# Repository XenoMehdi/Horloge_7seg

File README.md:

# Horloge_7seg
Affichage Horloge, calendrier et température sur un afficheur 7 segments LED geant

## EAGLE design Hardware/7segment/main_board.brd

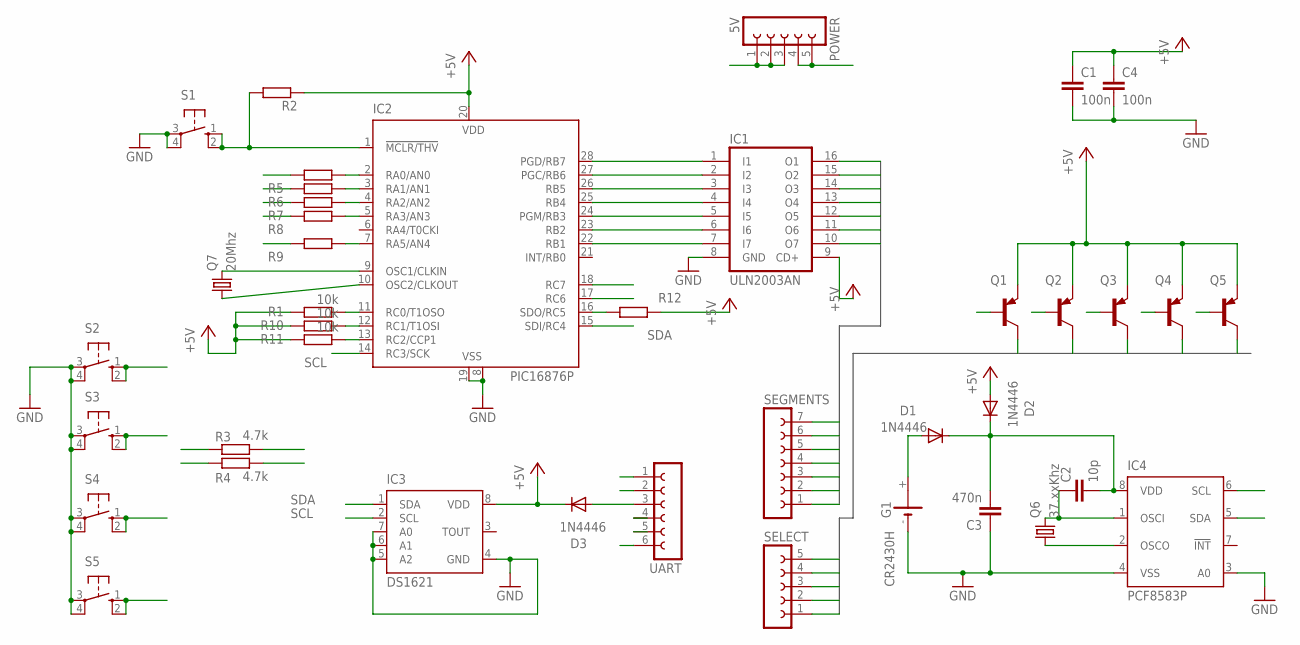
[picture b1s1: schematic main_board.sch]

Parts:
C1, C4: 100n; C025-030X050
C2: 10p; C025-030X050
C3: 470n; C025-030X050
D1, D2, D3: 1N4446; DO35-10
G1: CR2430H
IC1: ULN2003AN; DIL16
IC2: PIC16876P; DIL28-3
IC3: DS1621; DIL08
IC4: PCF8583P; DIL08
POWER: 5V; FE05-1
Q1, Q2, Q3, Q4, Q5: BC369; TO92-BCE
Q6: 37.xxKhz; TC38H
Q7: 20Mhz; HC49U-V
R1, R10, R11: 10k; 0204/7
R2, R5, R6, R7, R8, R9, R12: R-EU_0204/7; 0204/7
R3, R4: 4.7k; 0204/7
S1, S2, S3, S4, S5: 10-XX; B3F-10XX
SEGMENTS: FE07-1; FE07
SELECT: FE05-1
UART: FE06-1; FE06

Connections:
+5V: C1.1, C4.1, D2.A, D3.C, IC1.9 (CD+), IC2.20 (VDD), IC3.8 (VDD), POWER.1, POWER.2, POWER.3, Q1.E, Q2.E, Q3.E, Q4.E, Q5.E, R1.2, R2.1, R3.1, R4.1, R10.2, R11.2, R12.1
GND: C1.2, C3.1, C4.2, G1.-, IC1.8 (GND), IC2.8 (VSS), IC2.19 (VSS), IC3.4 (GND), IC3.5 (A2), IC3.6 (A1), IC3.7 (A0), IC4.3 (A0), IC4.4 (VSS), POWER.4, POWER.5, S1.3, S1.4 (P1), S2.3, S2.4 (P1), S3.3, S3.4 (P1), S4.3, S4.4 (P1), S5.3, S5.4 (P1), UART.1
J_SEG_DATA0: IC1.16 (O1), SEGMENTS.7
J_SEG_DATA1: IC1.15 (O2), SEGMENTS.6
J_SEG_DATA2: IC1.14 (O3), SEGMENTS.5
J_SEG_DATA3: IC1.13 (O4), SEGMENTS.4
J_SEG_DATA4: IC1.12 (O5), SEGMENTS.3
J_SEG_DATA5: IC1.11 (O6), SEGMENTS.2
J_SEG_DATA6: IC1.10 (O7), SEGMENTS.1
J_SEG_SELECT0: Q1.C, SELECT.5
J_SEG_SELECT1: Q2.C, SELECT.4
J_SEG_SELECT2: Q3.C, SELECT.3
J_SEG_SELECT3: Q4.C, SELECT.2
J_SEG_SELECT4: Q5.C, SELECT.1
unnamed: IC1.1 (I1), IC2.28 (PGD/RB7)
unnamed: IC1.2 (I2), IC2.27 (PGC/RB6)
unnamed: IC1.3 (I3), IC2.26 (RB5)
unnamed: IC1.4 (I4), IC2.25 (RB4)
unnamed: IC1.5 (I5), IC2.24 (PGM/RB3)
unnamed: C2.1, IC4.1 (OSCI), Q6.2
unnamed: IC1.7 (I7), IC2.22 (RB1)
unnamed: IC2.1 (!MCLR/THV), R2.2, S1.1 (S), S1.2 (S1)
unnamed: IC2.2 (RA0/AN0), R5.1
unnamed: IC2.10 (OSC2/CLKOUT), Q7.1
unnamed: IC4.2 (OSCO), Q6.1
unnamed: D1.A, G1.+
unnamed: IC1.6 (I6), IC2.23 (RB2)
unnamed: C2.2, C3.2, D1.C, D2.C, IC4.8 (VDD)
unnamed: IC2.9 (OSC1/CLKIN), Q7.2
unnamed: IC2.3 (RA1/AN1), R6.1
unnamed: IC2.4 (RA2/AN2), R7.1
unnamed: IC2.5 (RA3/AN3), R8.1
unnamed: IC2.7 (RA5/AN4), R9.1
unnamed: D3.A, UART.3
SCL: IC2.14 (RC3/SCK), IC3.2 (SCL), IC4.6 (SCL), R4.2
SDA: IC2.15 (SDI/RC4), IC3.1 (SDA), IC4.5 (SDA), R3.2
SEG1: Q1.B, R5.2
SEG2: Q2.B, R6.2
SEG3: Q3.B, R7.2
SEG4: Q4.B, R8.2
SEG5: Q5.B, R9.2
SW1: IC2.11 (RC0/T1OSO), R1.1, S2.1 (S), S2.2 (S1)
SW2: IC2.12 (RC1/T1OSI), R10.1, S3.1 (S), S3.2 (S1)
SW3: IC2.13 (RC2/CCP1), R11.1, S4.1 (S), S4.2 (S1)
SW4: IC2.16 (SDO/RC5), R12.2, S5.1 (S), S5.2 (S1)
UART_RX: IC2.18 (RC7), UART.4
UART_TX: IC2.17 (RC6), UART.5

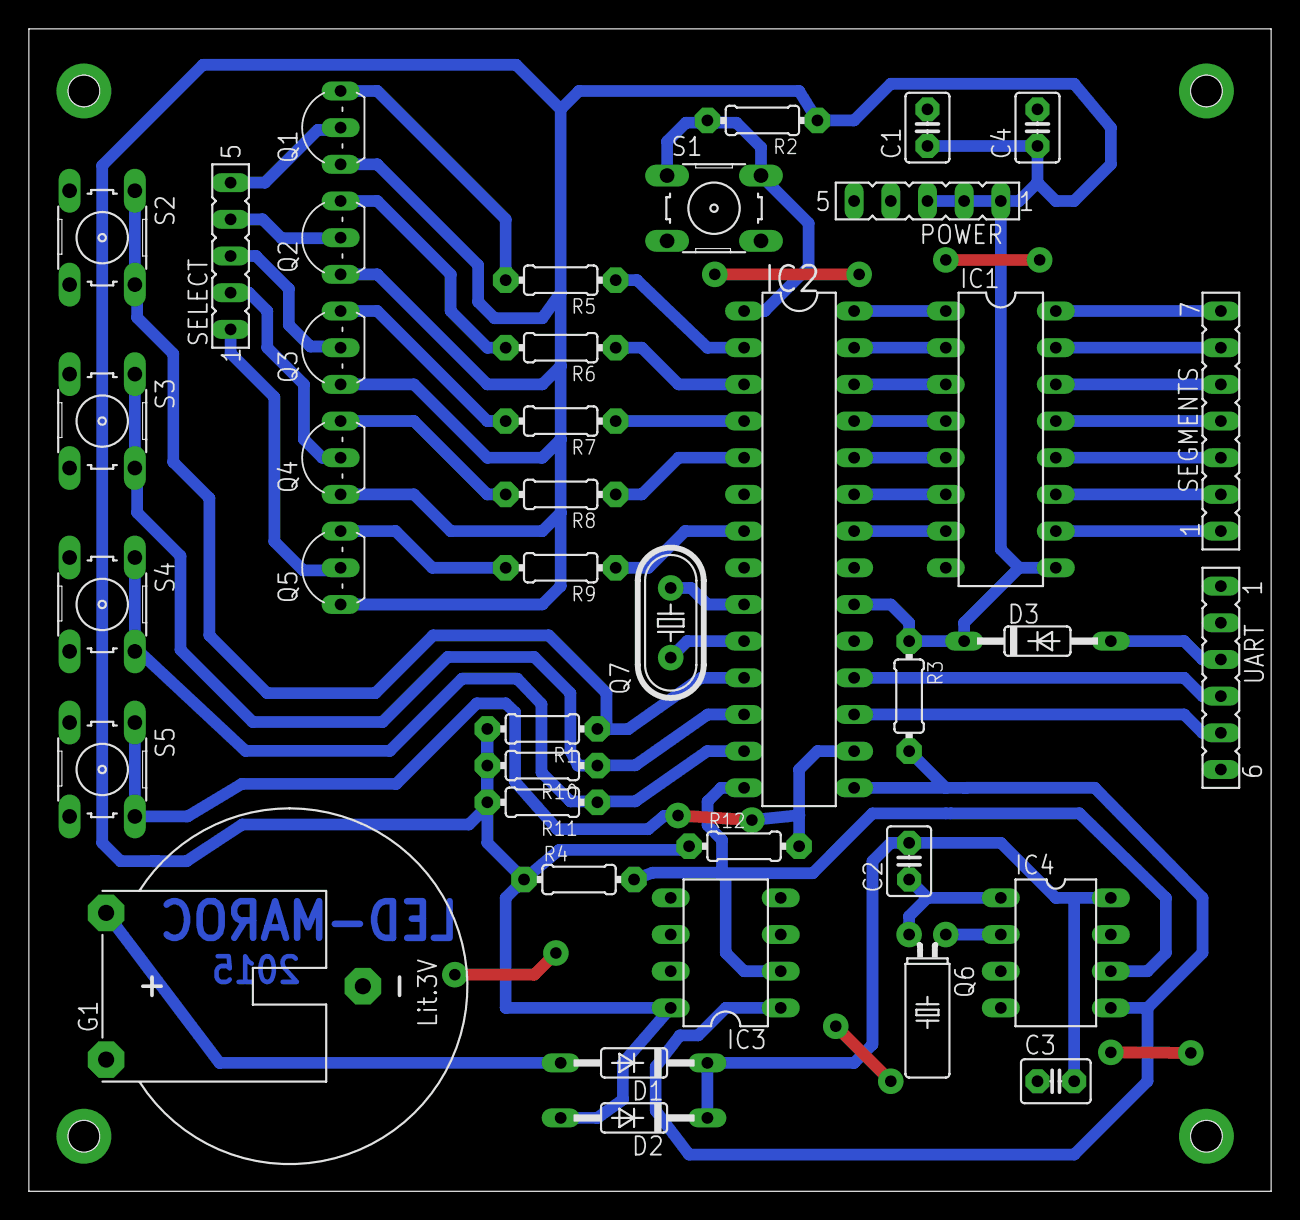
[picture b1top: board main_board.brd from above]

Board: 2 copper layers, 86.0 x 80.5 mm, 40 parts (0 on the bottom side), 47 nets.

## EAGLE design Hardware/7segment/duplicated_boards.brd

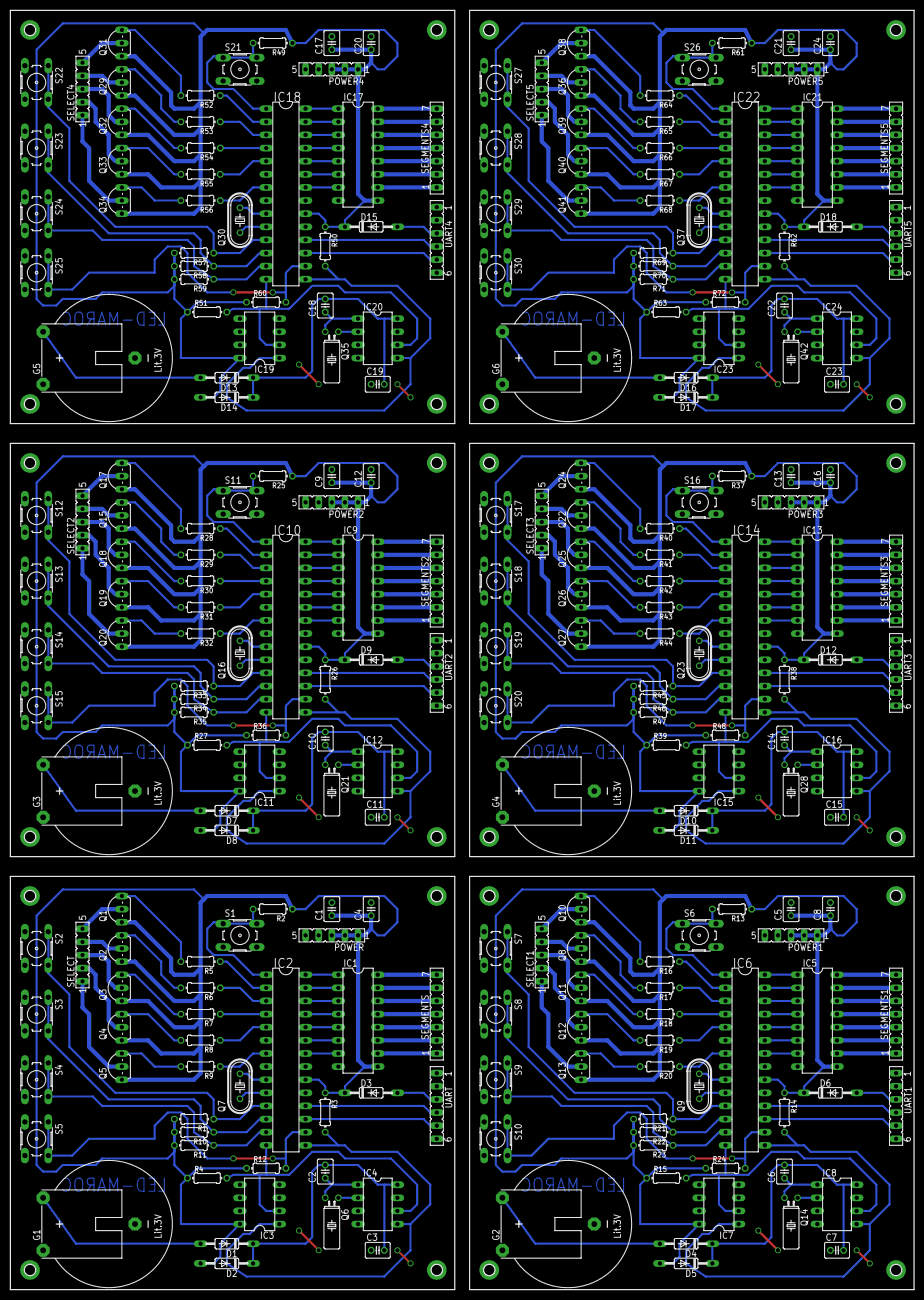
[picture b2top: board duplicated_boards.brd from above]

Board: 2 copper layers, 174.9 x 247.6 mm, 240 parts (0 on the bottom side), 282 nets.

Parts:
C1, C4, C5, C8, C9, C12, C13, C16, C17, C20, C21, C24: 100n; C025-030X050
C2, C6, C10, C14, C18, C22: 10p; C025-030X050
C3, C7, C11, C15, C19, C23: 470n; C025-030X050
D1, D2, D3, D4, D5, D6, D7, D8, D9, D10, D11, D12, D13, D14, D15, D16, D17, D18: 1N4446; DO35-10
G1, G2, G3, G4, G5, G6: CR2430H
IC1, IC5, IC9, IC13, IC17, IC21: ULN2003AN; DIL16
IC2, IC6, IC10, IC14, IC18, IC22: PIC16876P; DIL28-3
IC3, IC7, IC11, IC15, IC19, IC23: DS1621; DIL08
IC4, IC8, IC12, IC16, IC20, IC24: PCF8583P; DIL08
POWER, POWER1, POWER2, POWER3, POWER4, POWER5: 5V; FE05-1
Q1, Q2, Q3, Q4, Q5, Q8, Q10, Q11, Q12, Q13, Q15, Q17, Q18, Q19, Q20, Q22, Q24, Q25, Q26, Q27, Q29, Q31, Q32, Q33, Q34, Q36, Q38, Q39, Q40, Q41: BC369; TO92-BCE
Q6, Q14, Q21, Q28, Q35, Q42: 37.xxKhz; TC38H
Q7, Q9, Q16, Q23, Q30, Q37: 20Mhz; HC49U-V
R1, R10, R11, R21, R22, R23, R33, R34, R35, R45, R46, R47, R57, R58, R59, R69, R70, R71: 10k; 0204/7
R2, R5, R6, R7, R8, R9, R12, R13, R16, R17, R18, R19, R20, R24, R25, R28, R29, R30, R31, R32, R36, R37, R40, R41, R42, R43, R44, R48, R49, R52, R53, R54, R55, R56, R60, R61, R64, R65, R66, R67, R68, R72: 0204/7
R3, R4, R14, R15, R26, R27, R38, R39, R50, R51, R62, R63: 4.7k; 0204/7
S1, S2, S3, S4, S5, S6, S7, S8, S9, S10, S11, S12, S13, S14, S15, S16, S17, S18, S19, S20, S21, S22, S23, S24, S25, S26, S27, S28, S29, S30: B3F-10XX
SEGMENTS, SEGMENTS1, SEGMENTS2, SEGMENTS3, SEGMENTS4, SEGMENTS5: FE07
SELECT, SELECT1, SELECT2, SELECT3, SELECT4, SELECT5: FE05-1
UART, UART1, UART2, UART3, UART4, UART5: FE06

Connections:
+5V: C1.1, C4.1, D2.A, D3.C, IC1.9, IC2.20, IC3.8, POWER.1, POWER.2, POWER.3, Q1.E, Q2.E, Q3.E, Q4.E, Q5.E, R1.2, R2.1, R3.1, R4.1, R10.2, R11.2, R12.1
+5V1: C5.1, C8.1, D5.A, D6.C, IC5.9, IC6.20, IC7.8, POWER1.1, POWER1.2, POWER1.3, Q8.E, Q10.E, Q11.E, Q12.E, Q13.E, R13.1, R14.1, R15.1, R21.2, R22.2, R23.2, R24.1
+5V2: C9.1, C12.1, D8.A, D9.C, IC9.9, IC10.20, IC11.8, POWER2.1, POWER2.2, POWER2.3, Q15.E, Q17.E, Q18.E, Q19.E, Q20.E, R25.1, R26.1, R27.1, R33.2, R34.2, R35.2, R36.1
+5V3: C13.1, C16.1, D11.A, D12.C, IC13.9, IC14.20, IC15.8, POWER3.1, POWER3.2, POWER3.3, Q22.E, Q24.E, Q25.E, Q26.E, Q27.E, R37.1, R38.1, R39.1, R45.2, R46.2, R47.2, R48.1
+5V4: C17.1, C20.1, D14.A, D15.C, IC17.9, IC18.20, IC19.8, POWER4.1, POWER4.2, POWER4.3, Q29.E, Q31.E, Q32.E, Q33.E, Q34.E, R49.1, R50.1, R51.1, R57.2, R58.2, R59.2, R60.1
+5V5: C21.1, C24.1, D17.A, D18.C, IC21.9, IC22.20, IC23.8, POWER5.1, POWER5.2, POWER5.3, Q36.E, Q38.E, Q39.E, Q40.E, Q41.E, R61.1, R62.1, R63.1, R69.2, R70.2, R71.2, R72.1
GND: C1.2, C3.1, C4.2, G1.-, IC1.8, IC2.8, IC2.19, IC3.4, IC3.5, IC3.6, IC3.7, IC4.3, IC4.4, POWER.4, POWER.5, S1.3, S1.4, S2.3, S2.4, S3.3, S3.4, S4.3, S4.4, S5.3, S5.4, UART.1
GND1: C5.2, C7.1, C8.2, G2.-, IC5.8, IC6.8, IC6.19, IC7.4, IC7.5, IC7.6, IC7.7, IC8.3, IC8.4, POWER1.4, POWER1.5, S6.3, S6.4, S7.3, S7.4, S8.3, S8.4, S9.3, S9.4, S10.3, S10.4, UART1.1
GND2: C9.2, C11.1, C12.2, G3.-, IC9.8, IC10.8, IC10.19, IC11.4, IC11.5, IC11.6, IC11.7, IC12.3, IC12.4, POWER2.4, POWER2.5, S11.3, S11.4, S12.3, S12.4, S13.3, S13.4, S14.3, S14.4, S15.3, S15.4, UART2.1
GND3: C13.2, C15.1, C16.2, G4.-, IC13.8, IC14.8, IC14.19, IC15.4, IC15.5, IC15.6, IC15.7, IC16.3, IC16.4, POWER3.4, POWER3.5, S16.3, S16.4, S17.3, S17.4, S18.3, S18.4, S19.3, S19.4, S20.3, S20.4, UART3.1
GND4: C17.2, C19.1, C20.2, G5.-, IC17.8, IC18.8, IC18.19, IC19.4, IC19.5, IC19.6, IC19.7, IC20.3, IC20.4, POWER4.4, POWER4.5, S21.3, S21.4, S22.3, S22.4, S23.3, S23.4, S24.3, S24.4, S25.3, S25.4, UART4.1
GND5: C21.2, C23.1, C24.2, G6.-, IC21.8, IC22.8, IC22.19, IC23.4, IC23.5, IC23.6, IC23.7, IC24.3, IC24.4, POWER5.4, POWER5.5, S26.3, S26.4, S27.3, S27.4, S28.3, S28.4, S29.3, S29.4, S30.3, S30.4, UART5.1
J_SEG_DATA0: IC1.16, SEGMENTS.7
J_SEG_DATA1: IC1.15, SEGMENTS.6
J_SEG_DATA2: IC1.14, SEGMENTS.5
J_SEG_DATA3: IC1.13, SEGMENTS.4
J_SEG_DATA4: IC1.12, SEGMENTS.3
J_SEG_DATA5: IC1.11, SEGMENTS.2
J_SEG_DATA6: IC1.10, SEGMENTS.1
J_SEG_DATA7: IC5.16, SEGMENTS1.7
J_SEG_DATA8: IC5.15, SEGMENTS1.6
J_SEG_DATA9: IC5.14, SEGMENTS1.5
J_SEG_DATA10: IC5.13, SEGMENTS1.4
J_SEG_DATA11: IC5.12, SEGMENTS1.3
J_SEG_DATA12: IC5.11, SEGMENTS1.2
J_SEG_DATA13: IC5.10, SEGMENTS1.1
J_SEG_DATA14: IC9.16, SEGMENTS2.7
J_SEG_DATA15: IC9.15, SEGMENTS2.6
J_SEG_DATA16: IC9.14, SEGMENTS2.5
J_SEG_DATA17: IC9.13, SEGMENTS2.4
J_SEG_DATA18: IC9.12, SEGMENTS2.3
J_SEG_DATA19: IC9.11, SEGMENTS2.2
J_SEG_DATA20: IC9.10, SEGMENTS2.1
J_SEG_DATA21: IC13.16, SEGMENTS3.7
J_SEG_DATA22: IC13.15, SEGMENTS3.6
J_SEG_DATA23: IC13.14, SEGMENTS3.5
J_SEG_DATA24: IC13.13, SEGMENTS3.4
J_SEG_DATA25: IC13.12, SEGMENTS3.3
J_SEG_DATA26: IC13.11, SEGMENTS3.2
J_SEG_DATA27: IC13.10, SEGMENTS3.1
J_SEG_DATA28: IC17.16, SEGMENTS4.7
J_SEG_DATA29: IC17.15, SEGMENTS4.6
J_SEG_DATA30: IC17.14, SEGMENTS4.5
J_SEG_DATA31: IC17.13, SEGMENTS4.4
J_SEG_DATA32: IC17.12, SEGMENTS4.3
J_SEG_DATA33: IC17.11, SEGMENTS4.2
J_SEG_DATA34: IC17.10, SEGMENTS4.1
J_SEG_DATA35: IC21.16, SEGMENTS5.7
J_SEG_DATA36: IC21.15, SEGMENTS5.6
J_SEG_DATA37: IC21.14, SEGMENTS5.5
J_SEG_DATA38: IC21.13, SEGMENTS5.4
J_SEG_DATA39: IC21.12, SEGMENTS5.3
J_SEG_DATA40: IC21.11, SEGMENTS5.2
J_SEG_DATA41: IC21.10, SEGMENTS5.1
J_SEG_SELECT0: Q1.C, SELECT.5
J_SEG_SELECT1: Q2.C, SELECT.4
J_SEG_SELECT2: Q3.C, SELECT.3
J_SEG_SELECT3: Q4.C, SELECT.2
J_SEG_SELECT4: Q5.C, SELECT.1
J_SEG_SELECT5: Q8.C, SELECT1.4
J_SEG_SELECT6: Q13.C, SELECT1.1
J_SEG_SELECT7: Q10.C, SELECT1.5
J_SEG_SELECT8: Q11.C, SELECT1.3
J_SEG_SELECT9: Q12.C, SELECT1.2
J_SEG_SELECT10: Q15.C, SELECT2.4
J_SEG_SELECT11: Q20.C, SELECT2.1
J_SEG_SELECT12: Q17.C, SELECT2.5
J_SEG_SELECT13: Q18.C, SELECT2.3
J_SEG_SELECT14: Q19.C, SELECT2.2
J_SEG_SELECT15: Q22.C, SELECT3.4
J_SEG_SELECT16: Q27.C, SELECT3.1
J_SEG_SELECT17: Q24.C, SELECT3.5
J_SEG_SELECT18: Q25.C, SELECT3.3
J_SEG_SELECT19: Q26.C, SELECT3.2
J_SEG_SELECT20: Q29.C, SELECT4.4
J_SEG_SELECT21: Q34.C, SELECT4.1
J_SEG_SELECT22: Q31.C, SELECT4.5
J_SEG_SELECT23: Q32.C, SELECT4.3
J_SEG_SELECT24: Q33.C, SELECT4.2
J_SEG_SELECT25: Q36.C, SELECT5.4
J_SEG_SELECT26: Q41.C, SELECT5.1
J_SEG_SELECT27: Q38.C, SELECT5.5
J_SEG_SELECT28: Q39.C, SELECT5.3
J_SEG_SELECT29: Q40.C, SELECT5.2
unnamed: IC1.1, IC2.28
unnamed: IC1.2, IC2.27
unnamed: IC1.3, IC2.26
unnamed: IC1.4, IC2.25
unnamed: IC1.5, IC2.24
unnamed: C2.1, IC4.1, Q6.2
unnamed: IC1.7, IC2.22
unnamed: IC2.1, R2.2, S1.1, S1.2
unnamed: IC2.2, R5.1
unnamed: IC2.10, Q7.1
unnamed: IC4.2, Q6.1
unnamed: D1.A, G1.+
unnamed: IC1.6, IC2.23
unnamed: C2.2, C3.2, D1.C, D2.C, IC4.8
unnamed: IC2.9, Q7.2
unnamed: IC2.3, R6.1
unnamed: IC2.4, R7.1
unnamed: IC2.5, R8.1
unnamed: IC2.7, R9.1
unnamed: IC5.7, IC6.22
unnamed: D3.A, UART.3
unnamed: IC5.6, IC6.23
unnamed: IC5.5, IC6.24
unnamed: IC5.1, IC6.28
unnamed: IC5.2, IC6.27
unnamed: IC5.3, IC6.26
unnamed: IC5.4, IC6.25
unnamed: IC6.9, Q9.2
unnamed: IC6.10, Q9.1
unnamed: C6.1, IC8.1, Q14.2
unnamed: IC8.2, Q14.1
unnamed: D4.A, G2.+
unnamed: C6.2, C7.2, D4.C, D5.C, IC8.8
unnamed: IC6.1, R13.2, S6.1, S6.2
unnamed: D6.A, UART1.3
unnamed: IC6.2, R16.1
unnamed: IC6.3, R17.1
unnamed: IC6.5, R19.1
unnamed: IC6.7, R20.1
unnamed: IC6.4, R18.1
unnamed: IC9.7, IC10.22
unnamed: IC9.6, IC10.23
unnamed: IC9.5, IC10.24
unnamed: IC9.1, IC10.28
unnamed: IC9.2, IC10.27
unnamed: IC9.3, IC10.26
unnamed: IC9.4, IC10.25
unnamed: IC10.9, Q16.2
unnamed: IC10.10, Q16.1
unnamed: C10.1, IC12.1, Q21.2
unnamed: IC12.2, Q21.1
unnamed: D7.A, G3.+
unnamed: C10.2, C11.2, D7.C, D8.C, IC12.8
unnamed: IC10.1, R25.2, S11.1, S11.2
unnamed: D9.A, UART2.3
unnamed: IC10.2, R28.1
unnamed: IC10.3, R29.1
unnamed: IC10.5, R31.1
unnamed: IC10.7, R32.1
unnamed: IC10.4, R30.1
unnamed: IC13.7, IC14.22
unnamed: IC13.6, IC14.23
unnamed: IC13.5, IC14.24
unnamed: IC13.1, IC14.28
unnamed: IC13.2, IC14.27
unnamed: IC13.3, IC14.26
unnamed: IC13.4, IC14.25
unnamed: IC14.9, Q23.2
unnamed: IC14.10, Q23.1
unnamed: C14.1, IC16.1, Q28.2
unnamed: IC16.2, Q28.1
unnamed: D10.A, G4.+
unnamed: C14.2, C15.2, D10.C, D11.C, IC16.8
unnamed: IC14.1, R37.2, S16.1, S16.2
unnamed: D12.A, UART3.3
unnamed: IC14.2, R40.1
unnamed: IC14.3, R41.1
unnamed: IC14.5, R43.1
unnamed: IC14.7, R44.1
unnamed: IC14.4, R42.1
unnamed: IC17.7, IC18.22
unnamed: IC17.6, IC18.23
unnamed: IC17.5, IC18.24
unnamed: IC17.1, IC18.28
unnamed: IC17.2, IC18.27
unnamed: IC17.3, IC18.26
unnamed: IC17.4, IC18.25
unnamed: IC18.9, Q30.2
unnamed: IC18.10, Q30.1
unnamed: C18.1, IC20.1, Q35.2
unnamed: IC20.2, Q35.1
unnamed: D13.A, G5.+
unnamed: C18.2, C19.2, D13.C, D14.C, IC20.8
unnamed: IC18.1, R49.2, S21.1, S21.2
unnamed: D15.A, UART4.3
unnamed: IC18.2, R52.1
unnamed: IC18.3, R53.1
unnamed: IC18.5, R55.1
unnamed: IC18.7, R56.1
unnamed: IC18.4, R54.1
unnamed: IC21.7, IC22.22
unnamed: IC21.6, IC22.23
unnamed: IC21.5, IC22.24
unnamed: IC21.1, IC22.28
unnamed: IC21.2, IC22.27
unnamed: IC21.3, IC22.26
unnamed: IC21.4, IC22.25
unnamed: IC22.9, Q37.2
unnamed: IC22.10, Q37.1
unnamed: C22.1, IC24.1, Q42.2
unnamed: IC24.2, Q42.1
unnamed: D16.A, G6.+
unnamed: C22.2, C23.2, D16.C, D17.C, IC24.8
unnamed: IC22.1, R61.2, S26.1, S26.2
unnamed: D18.A, UART5.3
unnamed: IC22.2, R64.1
unnamed: IC22.3, R65.1
unnamed: IC22.5, R67.1
unnamed: IC22.7, R68.1
unnamed: IC22.4, R66.1
SCL: IC2.14, IC3.2, IC4.6, R4.2
SCL1: IC6.14, IC7.2, IC8.6, R15.2
SCL2: IC10.14, IC11.2, IC12.6, R27.2
SCL3: IC14.14, IC15.2, IC16.6, R39.2
SCL4: IC18.14, IC19.2, IC20.6, R51.2
SCL5: IC22.14, IC23.2, IC24.6, R63.2
SDA: IC2.15, IC3.1, IC4.5, R3.2
SDA1: IC6.15, IC7.1, IC8.5, R14.2
SDA2: IC10.15, IC11.1, IC12.5, R26.2
SDA3: IC14.15, IC15.1, IC16.5, R38.2
SDA4: IC18.15, IC19.1, IC20.5, R50.2
SDA5: IC22.15, IC23.1, IC24.5, R62.2
SEG1: Q1.B, R5.2
SEG2: Q2.B, R6.2
SEG3: Q3.B, R7.2
SEG4: Q4.B, R8.2
SEG5: Q5.B, R9.2
SEG6: Q10.B, R16.2
SEG7: Q11.B, R18.2
SEG8: Q13.B, R20.2
SEG9: Q8.B, R17.2
SEG10: Q12.B, R19.2
SEG11: Q17.B, R28.2
SEG12: Q18.B, R30.2
SEG13: Q20.B, R32.2
SEG14: Q15.B, R29.2
SEG15: Q19.B, R31.2
SEG16: Q24.B, R40.2
SEG17: Q25.B, R42.2
SEG18: Q27.B, R44.2
SEG19: Q22.B, R41.2
SEG20: Q26.B, R43.2
SEG21: Q31.B, R52.2
SEG22: Q32.B, R54.2
SEG23: Q34.B, R56.2
SEG24: Q29.B, R53.2
SEG25: Q33.B, R55.2
SEG26: Q38.B, R64.2
SEG27: Q39.B, R66.2
SEG28: Q41.B, R68.2
SEG29: Q36.B, R65.2
SEG30: Q40.B, R67.2
SW1: IC2.11, R1.1, S2.1, S2.2
SW2: IC2.12, R10.1, S3.1, S3.2
SW3: IC2.13, R11.1, S4.1, S4.2
SW4: IC2.16, R12.2, S5.1, S5.2
SW5: IC6.11, R21.1, S7.1, S7.2
SW6: IC6.12, R22.1, S8.1, S8.2
SW7: IC6.13, R23.1, S9.1, S9.2
SW8: IC6.16, R24.2, S10.1, S10.2
SW9: IC10.11, R33.1, S12.1, S12.2
SW10: IC10.12, R34.1, S13.1, S13.2
SW11: IC10.13, R35.1, S14.1, S14.2
SW12: IC10.16, R36.2, S15.1, S15.2
SW13: IC14.11, R45.1, S17.1, S17.2
SW14: IC14.12, R46.1, S18.1, S18.2
SW15: IC14.13, R47.1, S19.1, S19.2
SW16: IC14.16, R48.2, S20.1, S20.2
SW17: IC18.11, R57.1, S22.1, S22.2
SW18: IC18.12, R58.1, S23.1, S23.2
SW19: IC18.13, R59.1, S24.1, S24.2
SW20: IC18.16, R60.2, S25.1, S25.2
SW21: IC22.11, R69.1, S27.1, S27.2
SW22: IC22.12, R70.1, S28.1, S28.2
SW23: IC22.13, R71.1, S29.1, S29.2
SW24: IC22.16, R72.2, S30.1, S30.2
UART_RX: IC2.18, UART.4
UART_RX1: IC6.18, UART1.4
UART_RX2: IC10.18, UART2.4
UART_RX3: IC14.18, UART3.4
UART_RX4: IC18.18, UART4.4
UART_RX5: IC22.18, UART5.4
UART_TX: IC2.17, UART.5
UART_TX1: IC6.17, UART1.5
UART_TX2: IC10.17, UART2.5
UART_TX3: IC14.17, UART3.5
UART_TX4: IC18.17, UART4.5
UART_TX5: IC22.17, UART5.5

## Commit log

2015-06-03 Version 1
    1ère version du logiciel et de la carte.
